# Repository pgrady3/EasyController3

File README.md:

# EasyController3

*Update Feb 23, 2024 - The EasyController 3.2 has been released, which has been more thoroughly tested than the 3.0. Further tutorial videos and build guides are coming!*

The EasyController3 is the next evolution of the successful [EasyController2](https://github.com/pgrady3/EasyController2). The new version is cheaper, more efficient, and uses well-stocked components.

## Improvements over the EasyController2

* Reduced BOM cost from $70 to $43
* Uses more efficient synchronous PWM. Greater efficiency under partial throttle operation
* Improved from duty-cycle control to torque-control, improving controllability and reducing current spikes
* Added regenerative braking
* Lowered quiescent power from 960 mW to 280 mW in a typical installation
* Based on Raspberry Pi Pico microcontroller
* Uses more widely available surface-mount components

## Getting Started

For a comprehensive guide on how to build your own EasyController, please see the [getting started guide](/docs/getting-started.md).

## Background

The EasyController3 is a a simple brushless (BLDC) sensored motor controller (also known as an ESC, motor inverter, or motor drive). It is intended to power vehicles such as electric bikes, skateboards, or [Eco-Marathon vehicles](https://en.wikipedia.org/wiki/Shell_Eco-marathon) in the 50-1000 watt range. It is designed for hobbyists to assemble at home.

The EasyController family was built to to fill a gap in publicly released motor controller designs. It is designed to be simple yet still highly functional. It deliberately omits more complex features such as sensorless or field-oriented control, however these features can be added with modification. This project is meant as a learning tool and a foundation to potentially build more complex designs from.

## Specifications
* 8v-60v operation
* 20A continuous current, 40A burst (more with heatsinking)
* Large surface mount components designed to be hand-soldered by hobbyists
* Socket for automotive fuse
* Automatic hall sensor identification
* Simple, well-documented code. <400 lines with comments
* Torque or duty-cycle control
* Raspberry Pi Pico microcontroller, compatible with Windows/Mac/Linux
* DGD2304 gate drivers
* IRFB7730 MOSFETS
* BOM cost of $43 USD
* Open source under MIT License

## Schematic

## Board

## Software Used

* PCB layout: [Eagle](https://www.autodesk.com/products/eagle/free-download)
* Compiler: [RP2040 C SDK](https://datasheets.raspberrypi.com/pico/getting-started-with-pico.pdf) (see chapter 9)

## Other Related Controller Designs

There are several other open-source motor controller designs worth mentioning:
* The [VESC](https://vesc-project.com/) is a highly capable design, and is well suited for vehicle applications. However, due to the complexity and poorly written code, it is difficult to modify.
* The [Simple FOC](https://simplefoc.com/) project is an open-source library for FOC commutation. However, due to the hardware-agnostic code, it is low-performance and suited for gimbal motors, not vehicle applications.
* The [ODrive](https://odriverobotics.com/) is a modular controller built for robotics applications. However, the hardware is closed-source.

The EasyController3 is most suitable for people who want to design, build, and understand their own motor controller. If you'd just like to purchase something off-the-shelf, we recommend the VESC, which is around $100 USD.

## Contact Us

This controller was designed by [Patrick Grady](https://www.pgrady.net/), formerly with [Duke Electric Vehicles](https://www.duke-ev.org/). If you have a question that other users may also have, please open a GitHub issue. Alternatively, the best way to reach me is by email, at (first name).(last name)@outlook.com.

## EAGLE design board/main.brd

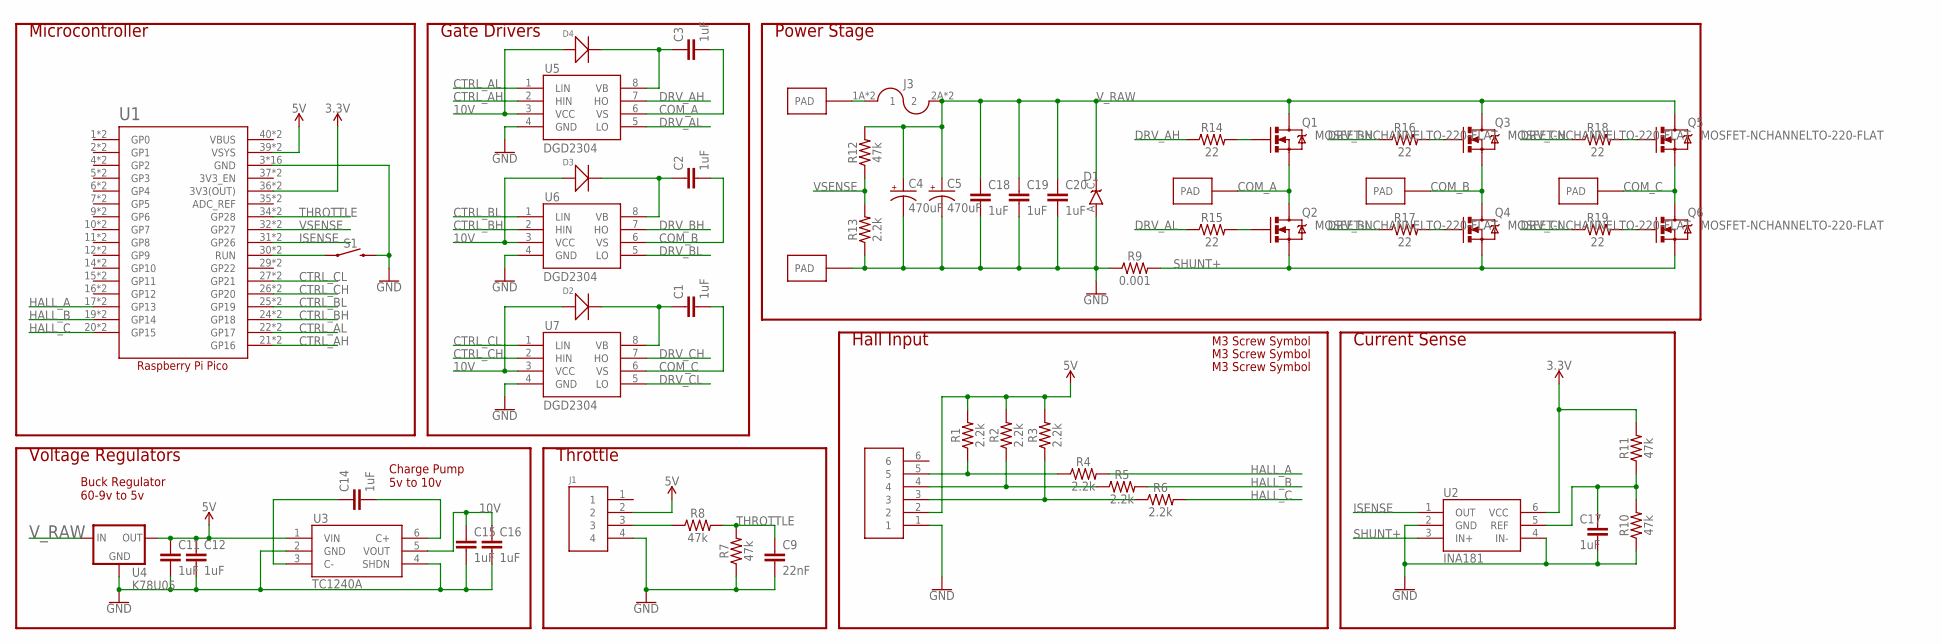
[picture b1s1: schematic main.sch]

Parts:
C1, C2, C3, C11, C12, C14, C15, C16, C17, C18, C19, C20: 1uF; 1206
C4, C5: 470uF; CPOL-RADIAL-5MM-10MM
C9: 22nF; 1206
D1: TVS; DO-214AC
D2, D3, D4: SMD-DIODE-100V-200MA(SOD-123); SOD-123
J1: HEADER4VALULOK; 4PINVALULOK
J2: HEADER6; 6PINVALULOK
J3: FUSE; AUTO_FUSE
Q1, Q2, Q3, Q4, Q5, Q6: MOSFET-NCHANNELTO-220-FLAT; TO-220-FLAT
R1, R2, R3, R4, R5, R6, R13: 2.2k; 1206
R7, R8, R10, R11, R12: 47k; 1206
R9: 0.001; R2512
R14, R15, R16, R17, R18, R19: 22; 1206
S1: MOMENTARY-SWITCH-SPST-PTH-6.0MM; TACTILE_SWITCH_PTH_6.0MM
U1: RASPBERRY_PICO-NO_DEBUG; PICO-PKG-NO_DEBUG
U2: INA181; SOT23-6
U3: TC1240A; SOT23-6
U4: K78U05; V78W_BACKWARDS
U5, U6, U7: DGD2304; SOIC8
U$4, U$5, U$6, U$7, U$8: PAD
U$10, U$11, U$12: SCREW; M3HOLE

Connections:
3.3V: R11.2, U1.36 (3V3(OUT)), U1.P$36 (3V3(OUT)), U2.6 (VCC)
5V: C11.1, C12.1, J1.2, J2.2, R1.2, R2.2, R3.2, U1.39 (VSYS), U1.P$39 (VSYS), U3.1 (VIN), U4.OUT
10V: C15.1, C16.1, D2.+, D3.+, D4.+, U3.5 (VOUT), U5.3 (VCC), U6.3 (VCC), U7.3 (VCC)
COM_A: C3.2, Q1.3 (S), Q2.2 (D), Q2.PAD (D), U5.6 (VS), U$6.PAD
COM_B: C2.2, Q3.3 (S), Q4.2 (D), Q4.PAD (D), U6.6 (VS), U$7.PAD
COM_C: C1.2, Q5.3 (S), Q6.2 (D), Q6.PAD (D), U7.6 (VS), U$8.PAD
CTRL_AH: U1.21 (GP16), U1.P$21 (GP16), U5.2 (HIN)
CTRL_AL: U1.22 (GP17), U1.P$22 (GP17), U5.1 (LIN)
CTRL_BH: U1.24 (GP18), U1.P$24 (GP18), U6.2 (HIN)
CTRL_BL: U1.25 (GP19), U1.P$25 (GP19), U6.1 (LIN)
CTRL_CH: U1.26 (GP20), U1.P$26 (GP20), U7.2 (HIN)
CTRL_CL: U1.27 (GP21), U1.P$27 (GP21), U7.1 (LIN)
DRV_AH: R14.1, U5.7 (HO)
DRV_AL: R15.1, U5.5 (LO)
DRV_BH: R16.1, U6.7 (HO)
DRV_BL: R17.1, U6.5 (LO)
DRV_CH: R18.1, U7.7 (HO)
DRV_CL: R19.1, U7.5 (LO)
GND: C4.-, C5.-, C9.2, C11.2, C12.2, C15.2, C16.2, C17.2, C18.2, C19.2, C20.2, D1.A, J1.4, J2.1, R7.1, R9.1, R10.1, R13.1, S1.3 (2), U1.3 (GND), U1.8 (GND), U1.13 (GND), U1.18 (GND), U1.23 (GND), U1.28 (GND), U1.33 (GND), U1.38 (GND), U1.P$3 (GND), U1.P$8 (GND), U1.P$13 (GND), U1.P$18 (GND), U1.P$23 (GND), U1.P$28 (GND), U1.P$33 (GND), U1.P$38 (GND), U2.2 (GND), U2.4 (IN-), U3.2 (GND), U3.4 (SHDN), U4.GND, U5.4 (GND), U6.4 (GND), U7.4 (GND), U$5.PAD
HALL_A: R4.2, U1.17 (GP13), U1.P$17 (GP13)
HALL_B: R5.2, U1.19 (GP14), U1.P$19 (GP14)
HALL_C: R6.2, U1.20 (GP15), U1.P$20 (GP15)
ISENSE: U1.31 (GP26), U1.P$31 (GP26), U2.1 (OUT)
unnamed: C2.1, D3.-, U6.8 (VB)
unnamed: J2.3, R3.1, R6.1
unnamed: C3.1, D4.-, U5.8 (VB)
unnamed: J2.4, R2.1, R5.1
unnamed: Q1.1 (G), R14.2
unnamed: J2.5, R1.1, R4.1
unnamed: J1.3, R8.1
unnamed: C1.1, D2.-, U7.8 (VB)
unnamed: S1.1, U1.30 (RUN), U1.P$30 (RUN)
unnamed: C17.1, R10.2, R11.1, U2.5 (REF)
unnamed: Q2.1 (G), R15.2
unnamed: Q3.1 (G), R16.2
unnamed: Q4.1 (G), R17.2
unnamed: Q5.1 (G), R18.2
unnamed: Q6.1 (G), R19.2
unnamed: C14.1, U3.3 (C-)
unnamed: C14.2, U3.6 (C+)
SHUNT+: Q2.3 (S), Q4.3 (S), Q6.3 (S), R9.2, U2.3 (IN+)
THROTTLE: C9.1, R7.2, R8.2, U1.34 (GP28), U1.P$34 (GP28)
VBUS: U1.40 (VBUS), U1.P$40 (VBUS)
VSENSE: R12.1, R13.2, U1.32 (GP27), U1.P$32 (GP27)
V_PREFUSE: J3.1A (1), J3.1B (1), U$4.PAD
V_RAW: C4.+, C5.+, C18.1, C19.1, C20.1, D1.C, J3.2A (2), J3.2B (2), Q1.2 (D), Q1.PAD (D), Q3.2 (D), Q3.PAD (D), Q5.2 (D), Q5.PAD (D), R12.2, U4.IN

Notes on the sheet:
Power Stage
Hall Input
Gate Drivers
Throttle
Microcontroller
Voltage Regulators
Current Sense
Buck Regulator 60-9v to 5v
Charge Pump 5v to 10v

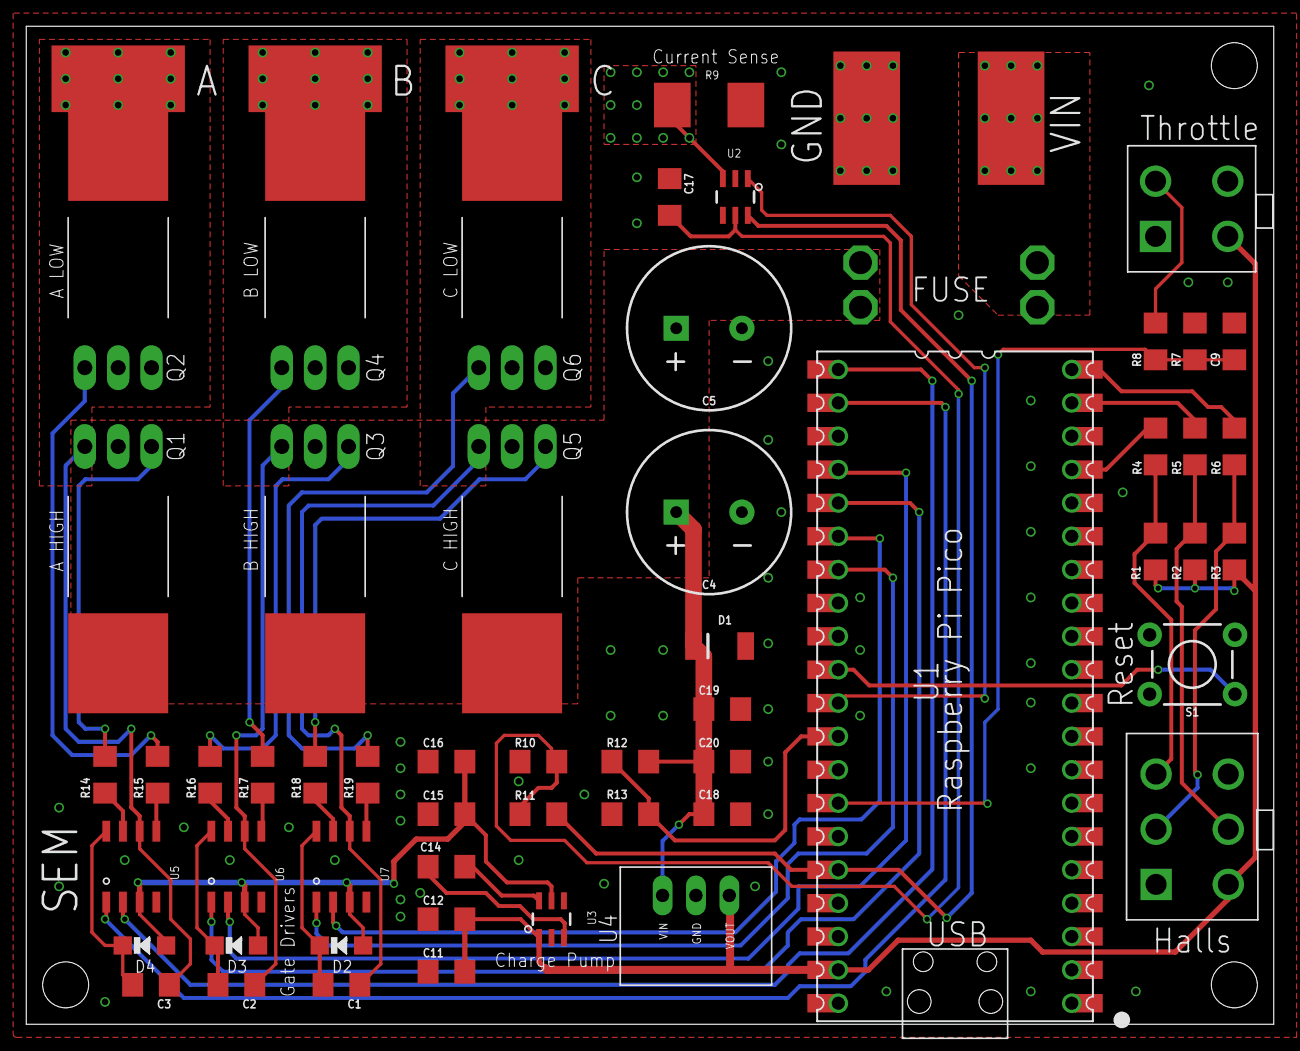
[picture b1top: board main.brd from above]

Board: 2 copper layers, 95.0 x 76.0 mm, 63 parts (0 on the bottom side), 46 nets.

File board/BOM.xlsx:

Digikey Part # | Mfg Part # | Description | Qty | Cost | Line Cost | Designator | Total Cost
2648-SC0915CT-ND | SC0915 | Raspberry Pi Pico | 1 | 4 | 4 | U1 | 43.219999999999992
IRFB7730PBF-ND | IRFB7730PBF | Power FETs | 6 | 3.25 | 19.5 | Q1,Q2,Q3,Q4,Q5,Q6
DGD2304S8-13DICT-ND | DGD2304S8-13 | Gate driver | 3 | 1.26 | 3.7800000000000002 | U5,U6,U7
SMD110PL-TPMSCT-ND | SMD110PL-TP | Diode for gate driver | 3 | 0.25 | 0.75 | D2,D3,D4
296-INA181A1QDBVRQ1CT-ND | INA181A1 | Current shunt amplifier | 1 | 0.57999999999999996 | 0.57999999999999996 | U2
RHM.001AUCT-ND | PMR100HZPFV1L00 | Current shunt resistor | 1 | 0.7 | 0.7 | R9
TC1240AECHCT-ND | TC1240AECHTR | Charge pump IC | 1 | 1.1100000000000001 | 1.1100000000000001 | U3
2725-K78U05-500R3-ND | K78U05-500R3 | 5V buck regulator | 1 | 2.89 | 2.89 | U4
1189-3684-ND | 100PX220MEFC12.5X20 | 220uF Capacitor | 2 | 1.1399999999999999 | 2.2799999999999998 | C4,C5
SMAJ60CALFCT-ND | SMAJ60CA | TVS Diode | 1 | 0.47 | 0.47 | D1
RMCF1206JT47K0CT-ND | RMCF1206JT47K0 | 47k Resistor | 5 | 0.03 | 0.15 | R7,R8,R10,R11,R12
RMCF1206JT2K20CT-ND | RMCF1206JT2K20 | 2.2k Resistor | 7 | 0.03 | 0.21 | R1,R2,R3,R4,R5,R6,R13
RMCF1206JT22R0CT-ND | RMCF1206JT22R0 | 22 Resistor | 6 | 0.03 | 0.18 | R14,R15,R16,R17,R18,R19
478-12061C223KAT4ACT-ND | 12061C223KAT4A | 22nF Capacitor | 1 | 0.08 | 0.08 | C9
1276-1838-1-ND | CL31B105KCHNNNE | 1uF Capacitor | 13 | 0.19 | 2.4700000000000002 | C1,C2,C3,C11,C12,C13,C14,C15,C16,C17,C18,C19,C20
36-3557-2-ND | 3557-2 | Fuse holder | 1 | 1.33 | 1.33 | J3
450-1650-ND | 1825910-6 | Reset pushbutton | 1 | 0.13 | 0.13 | S1
A30603-ND | 1586037-4 | 4 pin female VAL-U-LOK | 1 | 0.68 | 0.68 | J1
A30604-ND | 1586037-6 | 6 pin female VAL-U-LOK | 1 | 0.65 | 0.65 | J2
A30591-ND | 794954-4 | 4 pin male VAL-U-LOK | 1 | 0.21 | 0.21
A30592-ND | 794954-6 | 6 pin male VAL-U-LOK | 1 | 0.24 | 0.24
A99267CT-ND | 794956-1 | Crimp pin VAL-U-LOK | 10 | 0.05 | 0.5
F4202-ND | 0287030.PXCN | 30A fuse | 1 | 0.33 | 0.33

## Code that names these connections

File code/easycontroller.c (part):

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uint8_t hallToMotor[8] = {255, 255, 255, 255, 255, 255, 255, 255};  // Default hall table. Overwrite this with the output of the hall auto-identification 
// uint8_t hallToMotor[8] = {255, 2, 0, 1, 4, 3, 5, 255};  // Example hall table

const int THROTTLE_LOW = 600;               // ADC value corresponding to minimum throttle, 0-4095
const int THROTTLE_HIGH = 2650;             // ADC value corresponding to maximum throttle, 0-4095

const bool CURRENT_CONTROL = true;          // Use current control or duty cycle control
const int PHASE_MAX_CURRENT_MA = 6000;      // If using current control, the maximum phase current allowed
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const uint HALL_1_PIN = 13;
const uint HALL_2_PIN = 14;
const uint HALL_3_PIN = 15;
const uint ISENSE_PIN = 26;
const uint VSENSE_PIN = 27;
const uint THROTTLE_PIN = 28;

const uint A_PWM_SLICE = 0;
const uint B_PWM_SLICE = 1;
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
        if (throttle == 0)
        {
            duty_cycle = 0;     // If zero throttle, ignore the current control loop and turn all transistors off
            ticks_since_init = 0;   // Reset the timer since the transistors were turned on
        }
        else
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    gpio_set_function(CL_PIN, GPIO_FUNC_PWM);

    adc_init();
    adc_gpio_init(ISENSE_PIN);  // Set up ADC pins
    adc_gpio_init(VSENSE_PIN);
    adc_gpio_init(THROTTLE_PIN);

    sleep_ms(100);
    for(uint i = 0; i < ADC_BIAS_OVERSAMPLE; i++)   // Find the zero-current ADC reading. Reads the ADC multiple times and takes the average
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
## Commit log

2023-03-29 Duty cycle control works!
2023-03-30 Synchronous current-control works
2023-03-30 Tweaks
2023-03-30 Initial commit of docs
2023-03-30 Moved photo
2023-03-30 Added disclaimer to readme
2023-05-12 Updated readme, gate driver fix in works
2023-05-12 Clarified Readme
2023-12-05 Pointone update
2023-12-11 3.2 initial commit, changed FETs to TO-220s
2024-02-19 Code works
2024-02-23 Cleaned up code, added tons of comments
2024-02-23 Updated BOM
2024-02-23 Updated gerbers, docs, and images
2024-02-23 Remove matlab scripts

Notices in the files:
parts and their libraries:
SparkFun-Capacitors: Licensing: Creative Commons ShareAlike 4.0 International - https://creativecommons.org/licenses/by-sa/4.0
